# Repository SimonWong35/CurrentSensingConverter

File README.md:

## what is this module
CurrentSensingConverter is a module converts the current source of the sensors/peripherals from 4 to 20 mA to SPI format embedded system ready. 

### Schematic 

### Layout (36mm x 46mm)

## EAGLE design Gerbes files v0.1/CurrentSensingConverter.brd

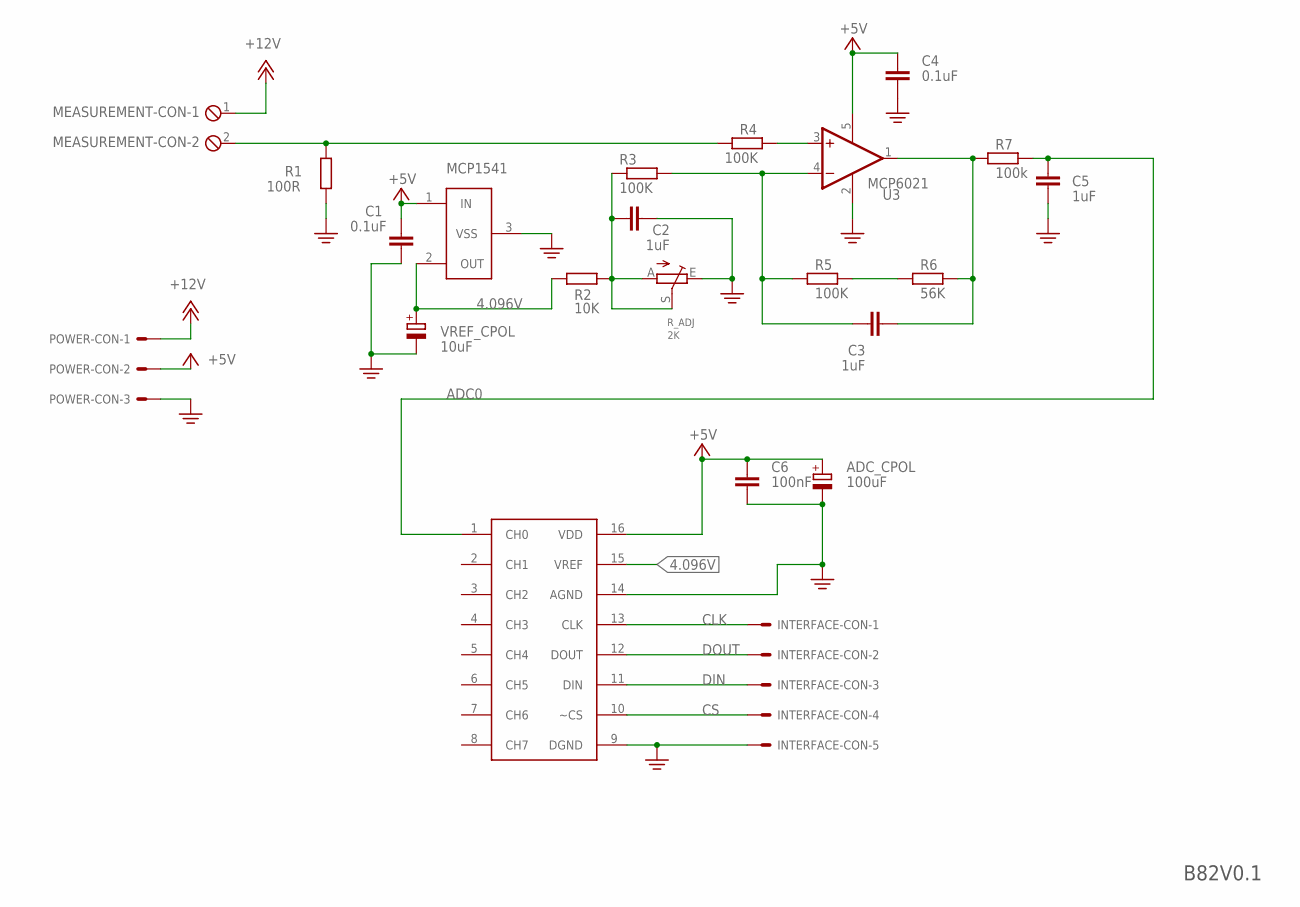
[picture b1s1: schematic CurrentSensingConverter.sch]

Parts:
ADC_CPOL: 100uF; D/7343-31R
C1, C4: 0.1uF; C1206
C2, C3, C5: 1uF; C1206
C6: 100nF; C1206
INTERFACE-CON: 22-05-7058-05; 7395-05
MCP3208: MCP3208-CI/SI; SO16
MEASUREMENT-CON: MPT2; 2POL254
POWER-CON: 22-05-7038-03; 7395-03
R1: 100R; R1206
R2: 10K; R1206
R3, R4, R5: 100K; R1206
R6: 56K; R1206
R7: 100k; R1206
R_ADJ: 2K; B25P
U1: U1; SOT23
U3: MCP6021; SOT23-5L
VREF_CPOL: 10uF; D/7343-31R

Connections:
4.096V: MCP3208.15 (VREF), R2.1, U1.2 (OUT), VREF_CPOL.+
+5V: ADC_CPOL.+, C1.1, C4.1, C6.1, MCP3208.16 (VDD), POWER-CON.2, U1.1 (IN), U3.5 (V+)
+12V: MEASUREMENT-CON.1, POWER-CON.1
ADC0: C5.1, MCP3208.1 (CH0), R7.2
CLK: INTERFACE-CON.1, MCP3208.13 (CLK)
CS: INTERFACE-CON.4, MCP3208.10 (~CS)
DIN: INTERFACE-CON.3, MCP3208.11 (DIN)
DOUT: INTERFACE-CON.2, MCP3208.12 (DOUT)
unnamed: C3.1, R3.2, R5.1, U3.4 (-IN)
unnamed: R5.2, R6.1
unnamed: C3.2, R6.2, R7.1, U3.1 (OUT)
unnamed: MEASUREMENT-CON.2, R1.2, R4.1
unnamed: R4.2, U3.3 (+IN)
unnamed: C2.1, R2.2, R3.1, R_ADJ.A, R_ADJ.S
PE: ADC_CPOL.-, C1.2, C2.2, C4.2, C5.2, C6.2, INTERFACE-CON.5, MCP3208.9 (DGND), MCP3208.14 (AGND), POWER-CON.3, R1.1, R_ADJ.E, U1.3 (VSS), U3.2 (V-), VREF_CPOL.-

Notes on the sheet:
B82V0.1

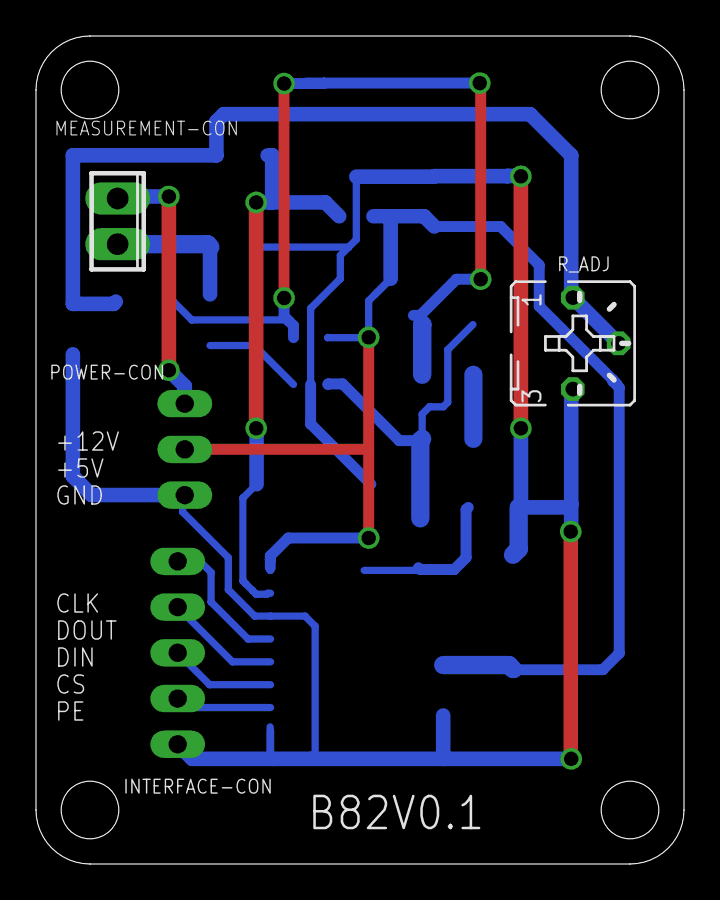
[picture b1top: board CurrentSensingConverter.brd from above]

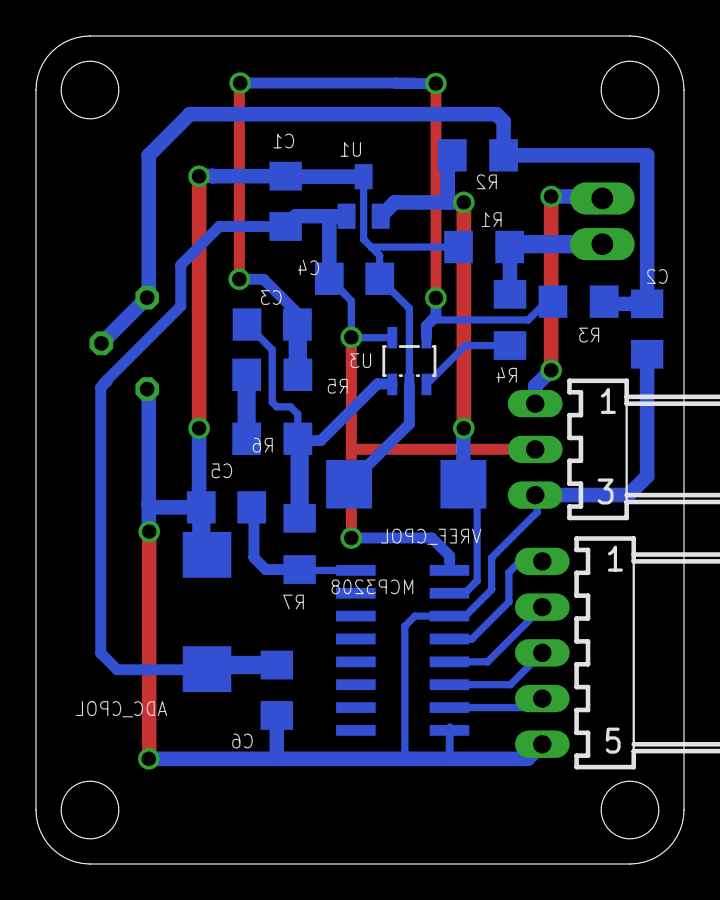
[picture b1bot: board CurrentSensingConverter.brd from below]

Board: 2 copper layers, 36.0 x 46.0 mm, 22 parts (20 on the bottom side), 15 nets.

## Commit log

2023-05-09 Create new file
